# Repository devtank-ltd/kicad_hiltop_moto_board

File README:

Copyright Devtank Ltd 2021.

This documentation describes Open Hardware and is Licensed under CERN-OHL-W v2.

You may redistribute and modify this documentation under the terms of the CERN-OHL-W v2 (https://cern.ch/cern-ohl). This documentation is distributed WITHOUT ANY EXPRESS OR IMPLIED WARRANTY, INCLUDING OF MERCHANTABILITY, SATISFACTORY QUALITY AND FITNESS FOR A PARTICULAR PURPOSE. Please see the CERN-OHL-W v2 for applicable conditions

Source location: git@github.com:devtank-ltd/kicad_hiltop_loti_board.git 

As per CERN-OHL-W v2 section 4.1, should You produce hardware based on these sources, You must maintain the Source Location visible on the external case of the HILTOP or other product you make using this documentation.

This folder contains HILTOP Moto Board hardware schematics and pcb layout files 

You will need Kicad to open hardware design files.

Moto Boards and other test and measurement products can be purchased directly from Devtank Ltd.

Please contact:
Tim Telford
CTO - Devtank Ltd
+44 (0)1332 650944

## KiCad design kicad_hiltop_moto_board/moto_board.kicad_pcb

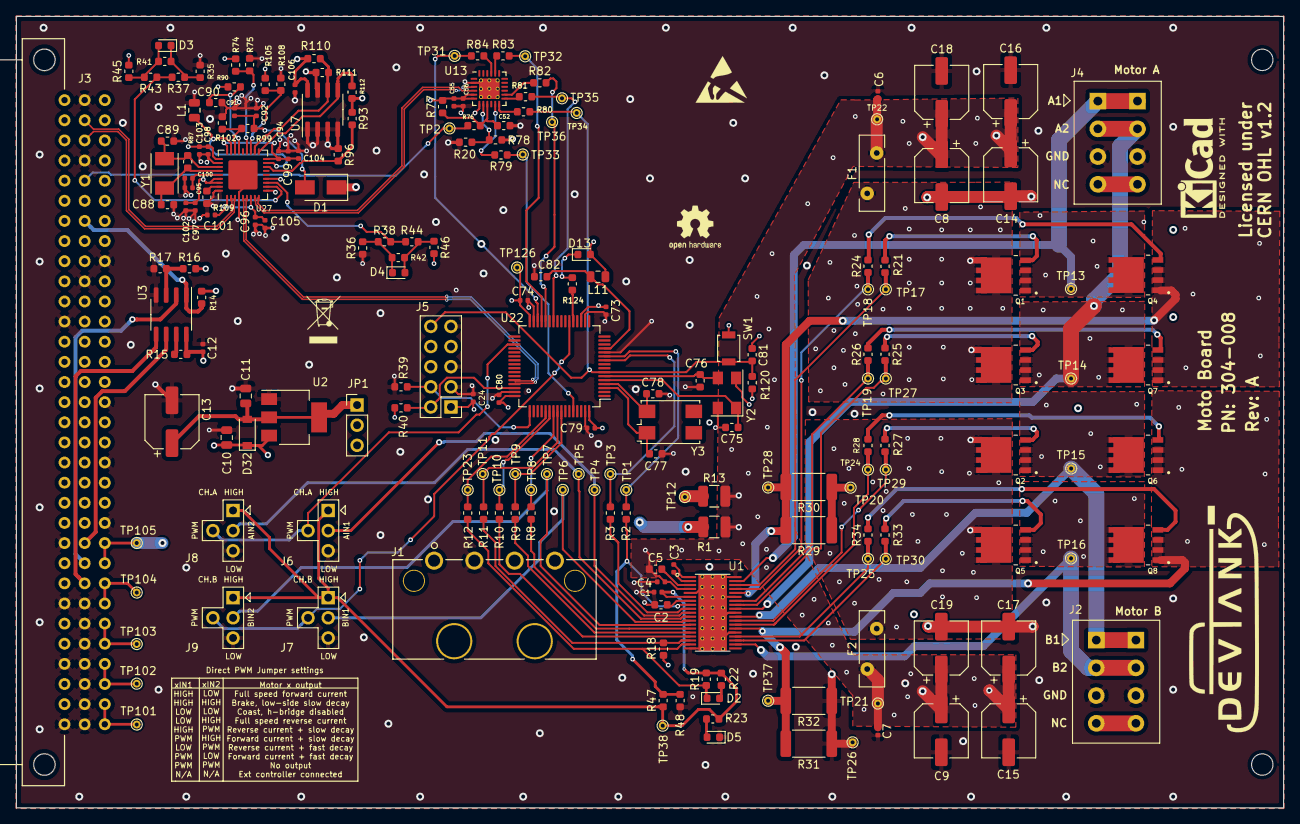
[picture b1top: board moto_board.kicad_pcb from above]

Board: 4 copper layers, 159.9 x 99.9 mm, 204 parts (0 on the bottom side), 117 nets.

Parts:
C1, C5: 1uF; C_0603_1608Metric
C2, C3, C6, C7, C92, C94, C95, C96, C97, C98, C99, C101: 0.1uF; C_0402_1005Metric
C4: 0.01uF; C_0402_1005Metric
C8, C9, C13, C14, C15, C16, C17, C18, C19: 100uF; CP_Elec_6.3x7.7
C10, C11: 10uF; C_0805_2012Metric
C12, C24, C56, C73, C74, C79, C80: 100nF; C_0402_1005Metric
C52: DNF; C_0603_1608Metric
C55, C100, C102, C103, C104, C105: 4.7uF; C_0402_1005Metric
C75, C76: 18pF; C_0603_1608Metric
C77, C78: 4.3pF; C_0603_1608Metric
C81, C82: 100nF; C_0603_1608Metric
C88, C89: 33pF; C_0603_1608Metric
C90: 0.1uF; C_0603_1608Metric
C91: 1.0uF; C_0402_1005Metric
C106: DNF; C_0402_1005Metric
D1: B240A-13; D_SMA
D2: RED; LED_0603_1608Metric
D3, D4, D5, D13: GRN; LED_0603_1608Metric
D32: MBR230LSFT1G; D_SOD-123
F1, F2: Polyfuse; Fuse_Bourns_MF-RHT200
J1: Conn_01x04; Molex_8981
J2, J4: Conn_01x04; Phoenix_Contact_SPTAF_4_way_terminal_block
J3: Conn_03x32_DIN41612; Socket_DIN41612-CaseC1-full-Male-96Pin-3rows_correct
J5: Conn_02x05_Top_Bottom; PinHeader_2x05_P2.54mm_Vertical
J6, J7, J8, J9: Conn_01x04; moto_board_4_pin_header
JP1: Jumper_NC_Dual; PinHeader_1x03_P2.54mm_Vertical
L1: 500mA/0.10DCR; L_0805_2012Metric
L11: 2A/0.05DCR; L_0805_2012Metric
Q1, Q2, Q3, Q4, Q5, Q6, Q7, Q8: CSD18540Q5B; TI_CSD18540Q5B
R1: DNF; R_1210_3225Metric
R2, R17, R37, R38, R45, R46, R48, R74, R77, R96, R108, R110, R112: DNF; R_0603_1608Metric
R3, R8, R9, R10, R11, R12, R21, R24, R25, R26, R27, R28, R33, R34, R35, R36, R76, R79, R80, R83, R84: 0R; R_0603_1608Metric
R13: 0R; R_1210_3225Metric
R14, R18, R19, R23, R47, R75, R99, R102, R105, R111, R120: 10K; R_0603_1608Metric
R15, R16: 4K7; R_0603_1608Metric
R20: 47K; R_0603_1608Metric
R22: 200R; R_0603_1608Metric
R29, R30, R31, R32: 0.015R; R_2512_6332Metric
R39, R40, R41, R42, R90, R93: 100K; R_0603_1608Metric
R43, R44, R81, R82, R124: 330R; R_0603_1608Metric
R78: 24K; R_0603_1608Metric
R87: 1M; R_0603_1608Metric
R109: 12.0K; R_0603_1608Metric
SW1: SW_Push; SW_SPST_B3U-1000P
TP1, TP2, TP3, TP4, TP5, TP6, TP7, TP8, TP9, TP10, TP11, TP12, TP13, TP14, TP15, TP16, TP17, TP18, TP19, TP20, TP21, TP22, TP23, TP24, TP25, TP26, TP27, TP28, TP29, TP30, TP31, TP32, TP33, TP34, TP35, TP36, TP37, TP38, TP101, TP102, TP103, TP104, TP105, TP126: Test_Point; TestPoint_THTPad_D1.0mm_Drill0.5mm
U1: DRV8704
U2: LD1117S33TR_SOT223; SOT-223-3_TabPin2
U3: AT25DN512CSSHF-B; SOIC-8_3.9x4.9mm_P1.27mm
U7: DNF; SOIC-8_3.9x4.9mm_P1.27mm
U13: CP2102N-A01-GQFN24; QFN-24-1EP_4x4mm_P0.5mm_EP2.6x2.6mm_ThermalVias
U22: STM32F072RBTx; LQFP-64_10x10mm_P0.5mm
U27: USB2502; QFN-36-1EP_6x6mm_P0.5mm_EP3.7x3.7mm
Y1: 50ppm 24.000MHZ; Crystal_SMD_TXC_7A-2Pin_5x3.2mm
Y2: 8MHZ; Crystal_SMD_Abracon_ABM3C-4Pin_5.0x3.2mm
Y3: ABS25-32.768KHZ-6-T; Crystal_SMD_7050-4Pin_7.0x5.0mm

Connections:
+3V3: C12.2, C24.1, C55.1, C56.1, C73.1, C74.1, C79.1, C80.1, C96.1, C97.1, C98.1, C101.1, C102.1, C103.1, C105.1, C106.1, D13.2, J5.1, JP1.2, L11.1, R14.2, R15.2, R16.2, R18.2, R40.1, R45.2, R46.2, R74.1, R77.2, R90.1, R93.1, R105.2, R110.2, R112.1, R120.1, TP126.1, U3.8, U7.8, U13.5, U13.6, U13.7, U22.19, U22.32, U22.48, U22.64, U27.1, U27.7, U27.13, U27.28, U27.33, U27.34
+3V3_BP: J3.7c, J3.8c, JP1.3, TP104.1
+3V3_LOC: C11.2, C13.1, D32.2, JP1.1, U2.2
+5V: C10.2, D1.1, D32.1, J3.3c, J3.4c, R78.2, TP102.1, U2.3
+12V: J3.1c, J3.2c, TP101.1
-5V: J3.5c, J3.6c, TP103.1
/12V_EXT: J1.1, R13.1, TP12.1
/A1: J4.1, Q1.1, Q4.3, TP13.1, U1.37
/A2: J4.2, Q3.1, Q7.3, TP14.1, U1.30
/B1: J2.1, Q2.1, Q6.3, TP15.1, U1.28
/B2: J2.2, Q5.1, Q8.3, TP16.1, U1.21
/M_AIN1: J6.2, TP4.1, U1.10
/M_AIN2: J8.2, TP5.1, U1.11
/M_BIN1: J7.2, TP6.1, U1.12
/M_BIN2: J9.2, TP7.1, U1.13
/M_FAULTn: R12.2, TP23.1, U22.53
/M_RESET: R3.2, TP3.1, U22.10
/M_SCLK: R8.2, TP8.1, U22.55
/M_SCS: R10.2, TP10.1, U22.54
/M_SDATI: R9.2, TP9.1, U22.57
/M_SDATO: R11.2, TP11.1, U22.56
/M_SLEEPn: R2.2, TP1.1, U22.11
/PORT_SEL: J3.26b, R14.1, U3.1
/PWM_1: J6.4, J8.4, U22.35
/PWM_2: J7.4, J9.4, U22.22
/RESET: J3.28b, R76.2, TP2.1
/SPI0_CLK: J3.10b, U3.6
/SPI0_MISO: J3.9b, U3.2
/SPI0_MOSI: J3.8b, U3.5
/STM_BOOT0: R79.1, TP33.1, U22.60
/STM_DEBUG_RX: R84.1, TP31.1, U22.30
/STM_DEBUG_TX: R83.1, TP32.1, U22.29
/STM_RES1: R81.1, TP35.1, U22.26
/STM_RES2: R82.1, TP36.1, U22.28
/STM_RESET: C81.1, J5.10, R80.1, R120.2, SW1.2, TP34.1, U22.7
/STM_USB_DATA_N: U22.44, U27.5
/STM_USB_DATA_P: U22.45, U27.6
/SWD_IO: J5.2, R40.2, U22.46
/SWD_SCK: J5.4, R39.1, U22.49
/USB_DATA_N: J3.30b, U27.3
/USB_DATA_P: J3.31b, U27.2
/USB_DEBUG_N: U13.4, U27.9
/USB_DEBUG_P: U13.3, U27.8
/V5: C2.1, J6.1, J7.1, J8.1, J9.1, R19.2, R22.1, R23.1, R47.1, TP38.1, U1.6
/VM: C4.2, C5.1, C6.1, C7.1, C8.1, C9.1, C14.1, C15.1, C16.1, C17.1, C18.1, C19.1, F1.2, F2.1, R1.2, R13.2, TP21.1, TP22.1, U1.4
/motor_control/FAULTn: D2.1, R12.1, R19.1, U1.18
/motor_control/RESET: R3.1, U1.9
/motor_control/SCLK: R8.1, U1.14
/motor_control/SCS: R10.1, U1.16
/motor_control/SDATI: R9.1, U1.15
/motor_control/SDATO: R11.1, R18.1, U1.17
/motor_control/SLEEPn: R2.1, R47.2, R48.2, U1.8
ADJ_DC: J3.9c, J3.10c, R1.1, TP105.1
GND: C1.1, C2.2, C4.1, C6.2, C7.2, C8.2, C9.2, C10.1, C11.1, C12.1, C13.2, C14.2, C15.2, C16.2, C17.2, C18.2, C19.2, C24.2, C52.2, C55.2, C56.2, C73.2, C74.2, C75.2, C76.2, C77.2, C78.2, C79.2, C80.2, C81.2, C82.2, C88.2, C89.1, C90.2, C91.2, C92.2, C94.2, C95.2, C96.2, C97.2, C98.2, C99.2, C100.2, C101.2, C102.2, C103.2, C104.2, C105.2, C106.2, D5.1, J1.2, J1.3, J2.3, J3.1a, J3.1b, J3.2b, J3.3b, J3.4a, J3.4b, J3.5b, J3.6b, J3.7a, J3.7b, J3.10a, J3.11c, J3.13b, J3.14c, J3.17c, J3.21a, J3.23b, J3.24c, J3.29b, J3.32b, J4.3, J5.3, J5.5, J5.9, J6.3, J7.3, J8.3, J9.3, L1.1, R17.1, R20.1, R29.1, R30.1, R31.1, R32.1, R35.1, R36.1, R39.2, R48.1, R75.1, R96.1, R102.2, R108.2, R109.2, R111.2, SW1.1, TP20.1, TP26.1, U1.5, U1.19, U1.24, U1.29, U1.33, U1.38, U1.39, U2.1, U3.4, U7.1, U7.2, U7.3, U7.4, U7.7, U13.2, U13.25, U22.12, U22.18, U22.31, U22.47, U22.63, U27.4, U27.10, U27.29, U27.36, U27.37, Y2.2, Y2.4
unnamed: C1.2, U1.7
unnamed: C3.1, U1.1
unnamed: C3.2, U1.2
unnamed: C5.2, U1.3
unnamed: C52.1, R76.1, R77.1, U13.9
unnamed: C75.1, U22.5, Y2.1
unnamed: C76.1, U22.6, Y2.3
unnamed: C77.1, U22.3, Y3.1
unnamed: C78.1, U22.4, Y3.4
unnamed: C82.1, L11.2, U22.13
unnamed: C88.1, R87.1, U27.31, Y1.2
unnamed: C89.2, R87.2, U27.30, Y1.1
unnamed: C90.1, R90.2, U27.24
unnamed: C91.1, C92.1, D1.2, R99.1
unnamed: C95.1, C100.1, U27.32
unnamed: C94.1, C99.1, C104.1, U27.18, U27.27
unnamed: D2.2, R22.2
unnamed: D3.1, R35.2, R37.1, R41.1
unnamed: D3.2, R41.2, R43.2, R45.1
unnamed: D4.1, R36.2, R38.1, R42.1
unnamed: D4.2, R42.2, R44.2, R46.1
unnamed: D5.2, R23.2
unnamed: D13.1, R124.1
unnamed: F1.1, Q1.3, Q3.3
unnamed: F2.2, Q2.3, Q5.3
unnamed: L1.2, U27.17, U27.26
unnamed: Q1.2, R21.2
unnamed: Q2.2, R27.2
unnamed: Q3.2, R25.2
unnamed: Q4.1, Q7.1, R29.2, R30.2, TP28.1, U1.34
unnamed: Q4.2, R24.2
unnamed: Q5.2, R33.2
unnamed: Q6.1, Q8.1, R31.2, R32.2, TP37.1, U1.25
unnamed: Q6.2, R28.2
unnamed: Q7.2, R26.2
unnamed: Q8.2, R34.2
unnamed: R15.1, U3.7
unnamed: R16.1, R17.2, U3.3
unnamed: R20.2, R78.1, U13.8
unnamed: R21.1, TP17.1, U1.36
unnamed: R24.1, TP18.1, U1.35
unnamed: R25.1, TP27.1, U1.31
unnamed: R26.1, TP19.1, U1.32
unnamed: R27.1, TP29.1, U1.27
unnamed: R28.1, TP24.1, U1.26
unnamed: R33.1, TP30.1, U1.22
unnamed: R34.1, TP25.1, U1.23
unnamed: R37.2, R43.1, U27.11
unnamed: R38.2, R44.1, U27.12
unnamed: R74.2, R75.2, U27.22
unnamed: R79.2, U13.11
unnamed: R80.2, U13.12
unnamed: R81.2, U13.13
unnamed: R82.2, U13.14
unnamed: R83.2, U13.20
unnamed: R84.2, U13.21
unnamed: R93.2, R96.2, U27.16
unnamed: R99.2, R102.1, U27.25
unnamed: R105.1, R108.1, U27.21
unnamed: R109.1, U27.35
unnamed: R110.1, R111.1, U7.6, U27.20
unnamed: R112.2, U7.5, U27.19
unnamed: R124.2, U22.21

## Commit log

2019-10-31 Setup common libraries for my Kicad project.
2019-10-31 merged fils into new repo
2019-10-31 Unused pind removed from moto board
2019-11-04 Started on moto board layout
2019-11-04 Rough layout of moto board
2019-11-08 Updated moto board schematic and layout
2019-11-08 Moto vboard test points added
2019-11-13 Moto board awaiting review
2019-11-15 Moto board connectors moved
2019-11-15 moto board 3d connector models added
2019-11-18 Updated moto board
2019-11-18 Moto board csd mosfet footprint changes
2019-11-18 Moto Board Rev A
2022-06-07 added bom
2022-10-13 Add license information.

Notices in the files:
kicad_hiltop_moto_board/moto_board.kicad_pcb:
CERN OHL v1.2
parts and their libraries:
Copyright 2016 Accelerated Designs. All rights reserved.
